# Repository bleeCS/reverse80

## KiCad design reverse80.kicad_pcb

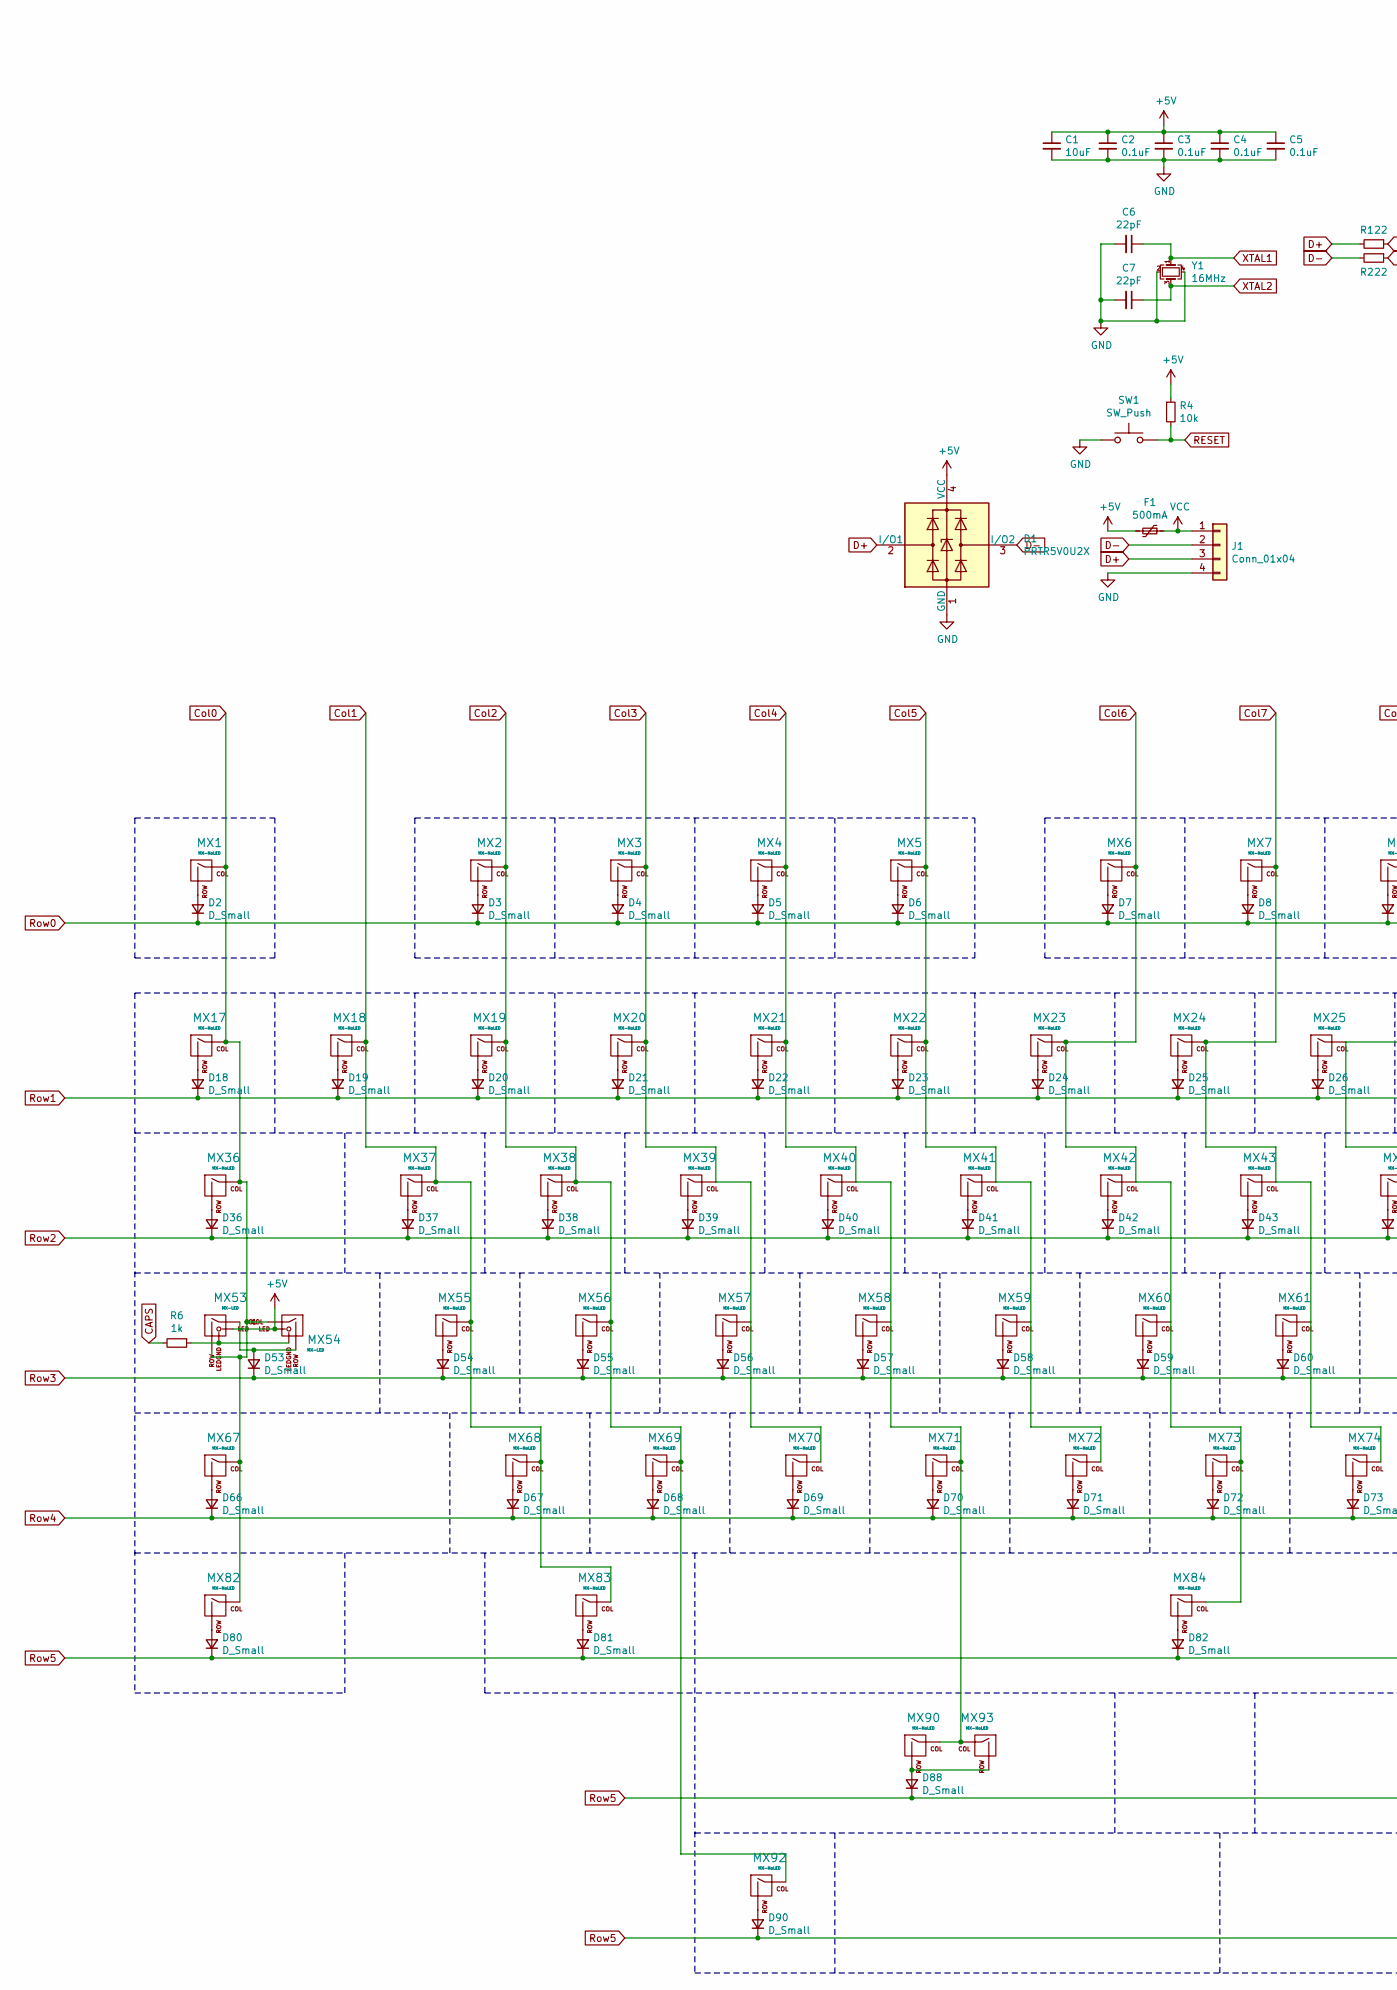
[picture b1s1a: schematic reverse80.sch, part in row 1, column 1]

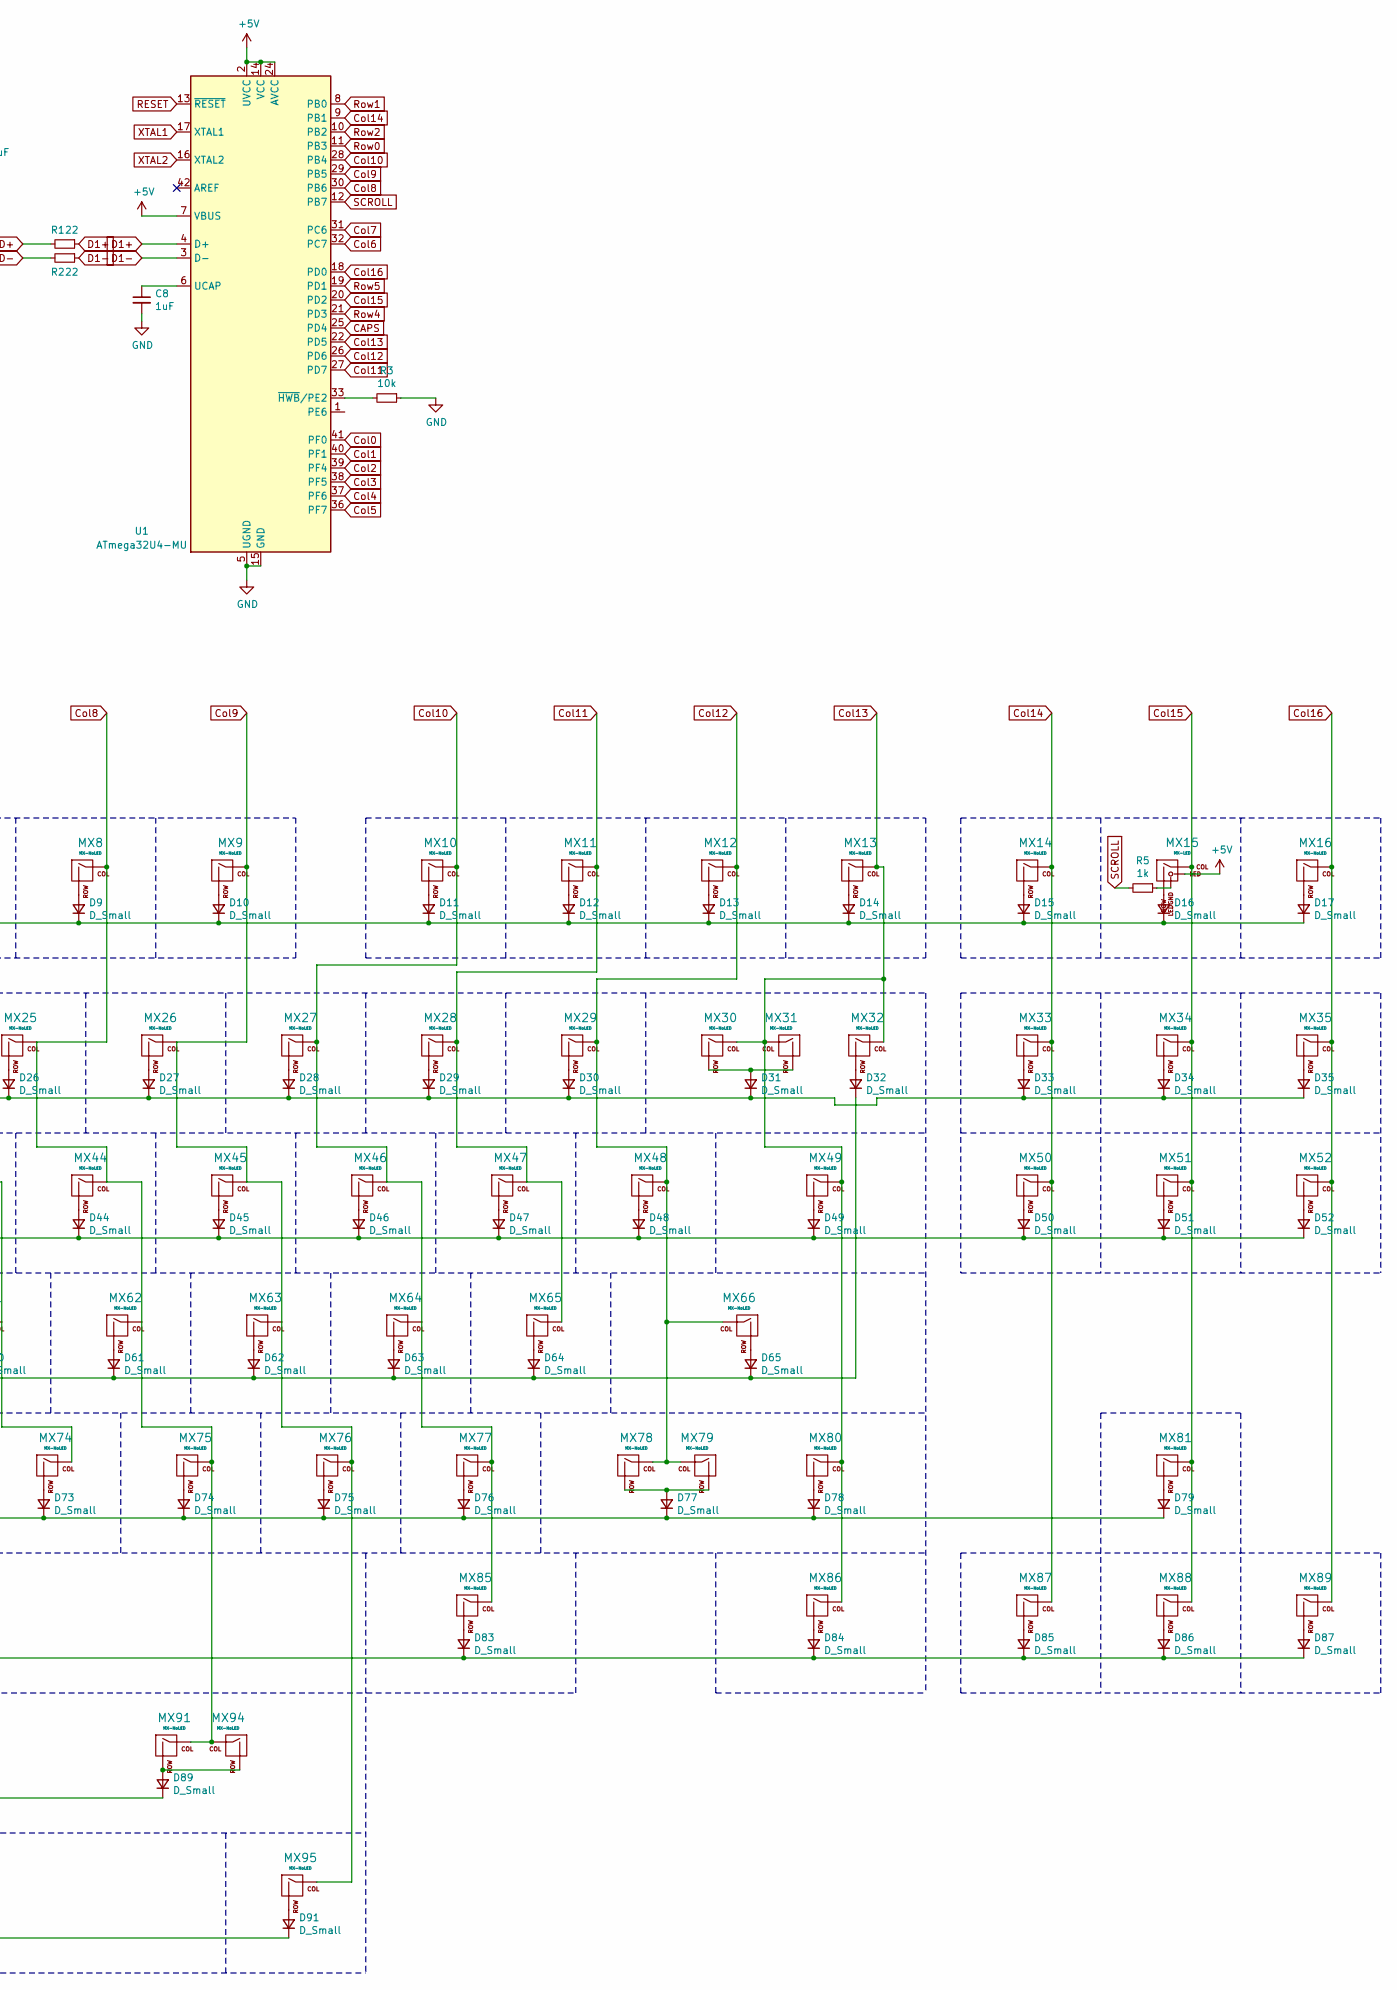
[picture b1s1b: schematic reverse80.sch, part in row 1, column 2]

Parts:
C1: 10uF; C_0603_1608Metric
C2, C3, C4, C5: 0.1uF; C_0603_1608Metric
C6, C7: 22pF; C_0603_1608Metric
C8: 1uF; C_0603_1608Metric
D1: PRTR5V0U2X; SOT143B
D2, D3, D4, D5, D6, D7, D8, D9, D10, D11, D12, D13, D14, D15, D16, D17, D18, D19, D20, D21, D22, D23, D24, D25, D26, D27, D28, D29, D30, D31, D32, D33, D34, D35, D36, D37, D38, D39, D40, D41, D42, D43, D44, D45, D46, D47, D48, D49, D50, D51, D52, D53, D54, D55, D56, D57, D58, D59, D60, D61, D62, D63, D64, D65, D66, D67, D68, D69, D70, D71, D72, D73, D74, D75, D76, D77, D78, D79, D80, D81, D82, D83, D84, D85, D86, D87, D88, D89, D90, D91: D_Small; D_SOD-123
F1: 500mA; Fuse_1206_3216Metric
J1: Conn_01x04; JST-SR-4
MX1, MX2, MX3, MX4, MX5, MX6, MX7, MX8, MX9, MX10, MX11, MX12, MX13, MX14, MX16, MX17, MX18, MX19, MX20, MX21, MX22, MX23, MX24, MX25, MX26, MX27, MX28, MX29, MX31, MX32, MX33, MX34, MX35, MX37, MX38, MX39, MX40, MX41, MX42, MX43, MX44, MX45, MX46, MX47, MX48, MX50, MX51, MX52, MX55, MX56, MX57, MX58, MX59, MX60, MX61, MX62, MX63, MX64, MX65, MX68, MX69, MX70, MX71, MX72, MX73, MX74, MX75, MX76, MX77, MX80, MX81, MX87, MX88, MX89, MX92, MX95: MX-NoLED; MXOnly-1U-NoLED
MX15: MX-LED; MXOnly-1U
MX30: MX-NoLED; MXOnly-2U-NoLED
MX36, MX49, MX82, MX83, MX85, MX86: MX-NoLED; MXOnly-1.5U-NoLED
MX53: MX-LED; MXOnly-1.25U-FLIPPED
MX54: MX-LED; MXOnly-1.75U
MX66, MX67, MX94: MX-NoLED; MXOnly-2.25U-NoLED
MX78: MX-NoLED; MXOnly-1.75U-NoLED
MX79, MX93: MX-NoLED; MXOnly-2.75U-NoLED
MX84: MX-NoLED; MXOnly-7U-NoLED
MX90, MX91: MX-NoLED; MXOnly-3U-NoLED
R1, R2: 22; R_0603_1608Metric
R3, R4: 10k; R_0603_1608Metric
R5, R6: 1k; R_0603_1608Metric
SW1: SW_Push; K2-1187SQ-A4SW-06
U1: ATmega32U4-MU; QFN-44-1EP_7x7mm_P0.5mm_EP5.2x5.2mm
Y1: 16MHz; Crystal_SMD_3225-4Pin_3.2x2.5mm

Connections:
+5V: C1.1, C2.1, C3.1, C4.1, C5.1, D1.4 (VCC), F1.2, MX15.3 (LED), MX53.3 (LED), MX54.3 (LED), R4.1, U1.2 (UVCC), U1.7 (VBUS), U1.14 (VCC), U1.24 (AVCC), U1.34 (VCC), U1.44 (AVCC)
CAPS: R6.2, U1.25 (PD4)
Col0: MX1.1 (COL), MX17.1 (COL), MX36.1 (COL), MX53.2 (ROW), MX54.1 (COL), MX67.1 (COL), MX82.1 (COL), U1.41 (PF0)
Col1: MX18.1 (COL), MX37.1 (COL), MX55.1 (COL), MX68.1 (COL), MX83.1 (COL), U1.40 (PF1)
Col2: MX2.1 (COL), MX19.1 (COL), MX38.1 (COL), MX56.1 (COL), MX69.1 (COL), MX92.1 (COL), U1.39 (PF4)
Col3: MX3.1 (COL), MX20.1 (COL), MX39.1 (COL), MX57.1 (COL), MX70.1 (COL), U1.38 (PF5)
Col4: MX4.1 (COL), MX21.1 (COL), MX40.1 (COL), MX58.1 (COL), MX71.1 (COL), MX90.1 (COL), MX93.1 (COL), U1.37 (PF6)
Col5: MX5.1 (COL), MX22.1 (COL), MX41.1 (COL), MX59.1 (COL), MX72.1 (COL), U1.36 (PF7)
Col6: MX6.1 (COL), MX23.1 (COL), MX42.1 (COL), MX60.1 (COL), MX73.1 (COL), MX84.1 (COL), U1.32 (PC7)
Col7: MX7.1 (COL), MX24.1 (COL), MX43.1 (COL), MX61.1 (COL), MX74.1 (COL), U1.31 (PC6)
Col8: MX8.1 (COL), MX25.1 (COL), MX44.1 (COL), MX62.1 (COL), MX75.1 (COL), MX91.1 (COL), MX94.1 (COL), U1.30 (PB6)
Col9: MX9.1 (COL), MX26.1 (COL), MX45.1 (COL), MX63.1 (COL), MX76.1 (COL), MX95.1 (COL), U1.29 (PB5)
Col10: MX10.1 (COL), MX27.1 (COL), MX46.1 (COL), MX64.1 (COL), MX77.1 (COL), MX85.1 (COL), U1.28 (PB4)
Col11: MX11.1 (COL), MX28.1 (COL), MX47.1 (COL), MX65.1 (COL), U1.27 (PD7)
Col12: MX12.1 (COL), MX29.1 (COL), MX48.1 (COL), MX66.1 (COL), MX78.1 (COL), MX79.1 (COL), U1.26 (PD6)
Col13: MX13.1 (COL), MX30.1 (COL), MX31.1 (COL), MX32.1 (COL), MX49.1 (COL), MX80.1 (COL), MX86.1 (COL), U1.22 (PD5)
Col14: MX14.1 (COL), MX33.1 (COL), MX50.1 (COL), MX87.1 (COL), U1.9 (PB1)
Col15: MX15.1 (COL), MX34.1 (COL), MX51.1 (COL), MX81.1 (COL), MX88.1 (COL), U1.20 (PD2)
Col16: MX16.1 (COL), MX35.1 (COL), MX52.1 (COL), MX89.1 (COL), U1.18 (PD0)
D1+: R1.1, U1.4 (D+)
D1-: R2.1, U1.3 (D-)
D+: D1.2 (I/O1), J1.3, R1.2
D-: D1.3 (I/O2), J1.2, R2.2
GND: C1.2, C2.2, C3.2, C4.2, C5.2, C6.2, C7.2, C8.2, D1.1 (GND), J1.4, R3.1, SW1.1, U1.5 (UGND), U1.15 (GND), U1.23 (GND), U1.35 (GND), U1.43 (GND), U1.45 (GND), Y1.2, Y1.4
unnamed: C8.1, U1.6 (UCAP)
unnamed: D2.2 (A), MX1.2 (ROW)
unnamed: D3.2 (A), MX2.2 (ROW)
unnamed: D4.2 (A), MX3.2 (ROW)
unnamed: D5.2 (A), MX4.2 (ROW)
unnamed: D6.2 (A), MX5.2 (ROW)
unnamed: D7.2 (A), MX6.2 (ROW)
unnamed: D8.2 (A), MX7.2 (ROW)
unnamed: D9.2 (A), MX8.2 (ROW)
unnamed: D10.2 (A), MX9.2 (ROW)
unnamed: D11.2 (A), MX10.2 (ROW)
unnamed: D12.2 (A), MX11.2 (ROW)
unnamed: D13.2 (A), MX12.2 (ROW)
unnamed: D14.2 (A), MX13.2 (ROW)
unnamed: D15.2 (A), MX14.2 (ROW)
unnamed: D16.2 (A), MX15.2 (ROW)
unnamed: D17.2 (A), MX16.2 (ROW)
unnamed: D18.2 (A), MX17.2 (ROW)
unnamed: D19.2 (A), MX18.2 (ROW)
unnamed: D20.2 (A), MX19.2 (ROW)
unnamed: D21.2 (A), MX20.2 (ROW)
unnamed: D22.2 (A), MX21.2 (ROW)
unnamed: D23.2 (A), MX22.2 (ROW)
unnamed: D24.2 (A), MX23.2 (ROW)
unnamed: D25.2 (A), MX24.2 (ROW)
unnamed: D26.2 (A), MX25.2 (ROW)
unnamed: D27.2 (A), MX26.2 (ROW)
unnamed: D28.2 (A), MX27.2 (ROW)
unnamed: D29.2 (A), MX28.2 (ROW)
unnamed: D30.2 (A), MX29.2 (ROW)
unnamed: D31.2 (A), MX30.2 (ROW), MX31.2 (ROW)
unnamed: D32.2 (A), MX32.2 (ROW)
unnamed: D33.2 (A), MX33.2 (ROW)
unnamed: D34.2 (A), MX34.2 (ROW)
unnamed: D35.2 (A), MX35.2 (ROW)
unnamed: D36.2 (A), MX36.2 (ROW)
unnamed: D37.2 (A), MX37.2 (ROW)
unnamed: D38.2 (A), MX38.2 (ROW)
unnamed: D39.2 (A), MX39.2 (ROW)
unnamed: D40.2 (A), MX40.2 (ROW)
unnamed: D41.2 (A), MX41.2 (ROW)
unnamed: D42.2 (A), MX42.2 (ROW)
unnamed: D43.2 (A), MX43.2 (ROW)
unnamed: D44.2 (A), MX44.2 (ROW)
unnamed: D45.2 (A), MX45.2 (ROW)
unnamed: D46.2 (A), MX46.2 (ROW)
unnamed: D47.2 (A), MX47.2 (ROW)
unnamed: D48.2 (A), MX48.2 (ROW)
unnamed: D49.2 (A), MX49.2 (ROW)
unnamed: D50.2 (A), MX50.2 (ROW)
unnamed: D51.2 (A), MX51.2 (ROW)
unnamed: D52.2 (A), MX52.2 (ROW)
unnamed: D53.2 (A), MX53.1 (COL), MX54.2 (ROW)
unnamed: D54.2 (A), MX55.2 (ROW)
unnamed: D55.2 (A), MX56.2 (ROW)
unnamed: D56.2 (A), MX57.2 (ROW)
unnamed: D57.2 (A), MX58.2 (ROW)
unnamed: D58.2 (A), MX59.2 (ROW)
unnamed: D59.2 (A), MX60.2 (ROW)
unnamed: D60.2 (A), MX61.2 (ROW)
unnamed: D61.2 (A), MX62.2 (ROW)
unnamed: D62.2 (A), MX63.2 (ROW)
unnamed: D63.2 (A), MX64.2 (ROW)
unnamed: D64.2 (A), MX65.2 (ROW)
unnamed: D65.2 (A), MX66.2 (ROW)
unnamed: D66.2 (A), MX67.2 (ROW)
unnamed: D67.2 (A), MX68.2 (ROW)
unnamed: D68.2 (A), MX69.2 (ROW)
unnamed: D69.2 (A), MX70.2 (ROW)
unnamed: D70.2 (A), MX71.2 (ROW)
unnamed: D71.2 (A), MX72.2 (ROW)
unnamed: D72.2 (A), MX73.2 (ROW)
unnamed: D73.2 (A), MX74.2 (ROW)
unnamed: D74.2 (A), MX75.2 (ROW)
unnamed: D75.2 (A), MX76.2 (ROW)
unnamed: D76.2 (A), MX77.2 (ROW)
unnamed: D77.2 (A), MX78.2 (ROW), MX79.2 (ROW)
unnamed: D78.2 (A), MX80.2 (ROW)
unnamed: D79.2 (A), MX81.2 (ROW)
unnamed: D80.2 (A), MX82.2 (ROW)
unnamed: D81.2 (A), MX83.2 (ROW)
unnamed: D82.2 (A), MX84.2 (ROW)
unnamed: D83.2 (A), MX85.2 (ROW)
unnamed: D84.2 (A), MX86.2 (ROW)
unnamed: D85.2 (A), MX87.2 (ROW)
unnamed: D86.2 (A), MX88.2 (ROW)
unnamed: D87.2 (A), MX89.2 (ROW)
unnamed: D88.2 (A), MX90.2 (ROW), MX93.2 (ROW)
unnamed: D89.2 (A), MX91.2 (ROW), MX94.2 (ROW)
unnamed: D90.2 (A), MX92.2 (ROW)
unnamed: D91.2 (A), MX95.2 (ROW)
unnamed: MX15.4 (LEDGND), R5.1
unnamed: MX53.4 (LEDGND), MX54.4 (LEDGND), R6.1
unnamed: R3.2, U1.33 (~HWB~/PE2)
RESET: R4.2, SW1.2, U1.13 (~RESET)
Row0: D2.1 (K), D3.1 (K), D4.1 (K), D5.1 (K), D6.1 (K), D7.1 (K), D8.1 (K), D9.1 (K), D10.1 (K), D11.1 (K), D12.1 (K), D13.1 (K), D14.1 (K), D15.1 (K), D16.1 (K), D17.1 (K), U1.11 (PB3)
Row1: D18.1 (K), D19.1 (K), D20.1 (K), D21.1 (K), D22.1 (K), D23.1 (K), D24.1 (K), D25.1 (K), D26.1 (K), D27.1 (K), D28.1 (K), D29.1 (K), D30.1 (K), D31.1 (K), D33.1 (K), D34.1 (K), D35.1 (K), U1.8 (PB0)
Row2: D36.1 (K), D37.1 (K), D38.1 (K), D39.1 (K), D40.1 (K), D41.1 (K), D42.1 (K), D43.1 (K), D44.1 (K), D45.1 (K), D46.1 (K), D47.1 (K), D48.1 (K), D49.1 (K), D50.1 (K), D51.1 (K), D52.1 (K), U1.10 (PB2)
Row3: D32.1 (K), D53.1 (K), D54.1 (K), D55.1 (K), D56.1 (K), D57.1 (K), D58.1 (K), D59.1 (K), D60.1 (K), D61.1 (K), D62.1 (K), D63.1 (K), D64.1 (K), D65.1 (K)
Row4: D66.1 (K), D67.1 (K), D68.1 (K), D69.1 (K), D70.1 (K), D71.1 (K), D72.1 (K), D73.1 (K), D74.1 (K), D75.1 (K), D76.1 (K), D77.1 (K), D78.1 (K), D79.1 (K), U1.21 (PD3)
Row5: D80.1 (K), D81.1 (K), D82.1 (K), D83.1 (K), D84.1 (K), D85.1 (K), D86.1 (K), D87.1 (K), D88.1 (K), D89.1 (K), D90.1 (K), D91.1 (K), U1.19 (PD1)
SCROLL: R5.2, U1.12 (PB7)
VCC: F1.1, J1.1
XTAL1: C6.1, U1.17 (XTAL1), Y1.1
XTAL2: C7.1, U1.16 (XTAL2), Y1.3

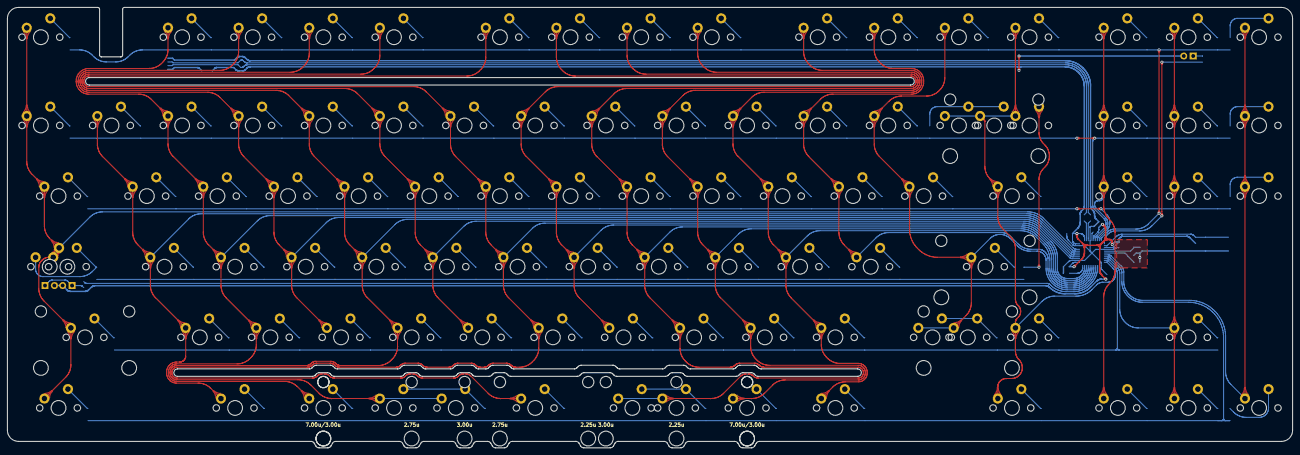
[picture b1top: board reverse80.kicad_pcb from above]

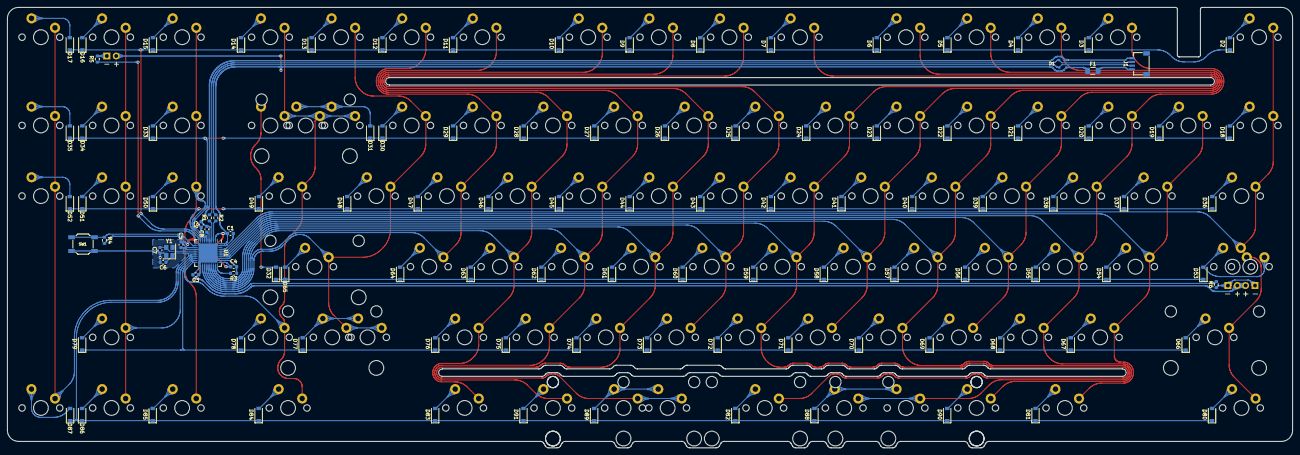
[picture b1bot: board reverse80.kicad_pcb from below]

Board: 2 copper layers, 346.7 x 118.8 mm, 205 parts (110 on the bottom side), 129 nets.

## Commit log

2021-09-15 initialize project
2021-09-15 add submodules and .gitignore
2021-09-22 completed pcb
